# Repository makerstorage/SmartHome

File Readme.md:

This repo is for our iot products

And our store at

http://makerstorage.com/index.php

We enjoy sharing theses ideas with you all and any contributions, comments and or feedback is invited.

Community, Collaboration and Sharing is our most important assets.

This Project is Open Source and is licensed under the Creative Commons 3.0.

https://creativecommons.org/licenses/by-sa/3.0/

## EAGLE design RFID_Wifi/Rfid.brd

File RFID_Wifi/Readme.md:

RFID WIFI Board

For more details, check out the product pages at

http://makerstorage.com/index.php?id_product=26&controller=product

MakerStorage invests time and resources providing this open source design, please support MakerStorage and open-source hardware by purchasing products from MakerStorage!

Designed by MakerStorage LLC.

Creative Commons Attribution, Share-Alike license, check https://creativecommons.org/licenses/by-sa/3.0/ for more information All text above must be included in any redistribution

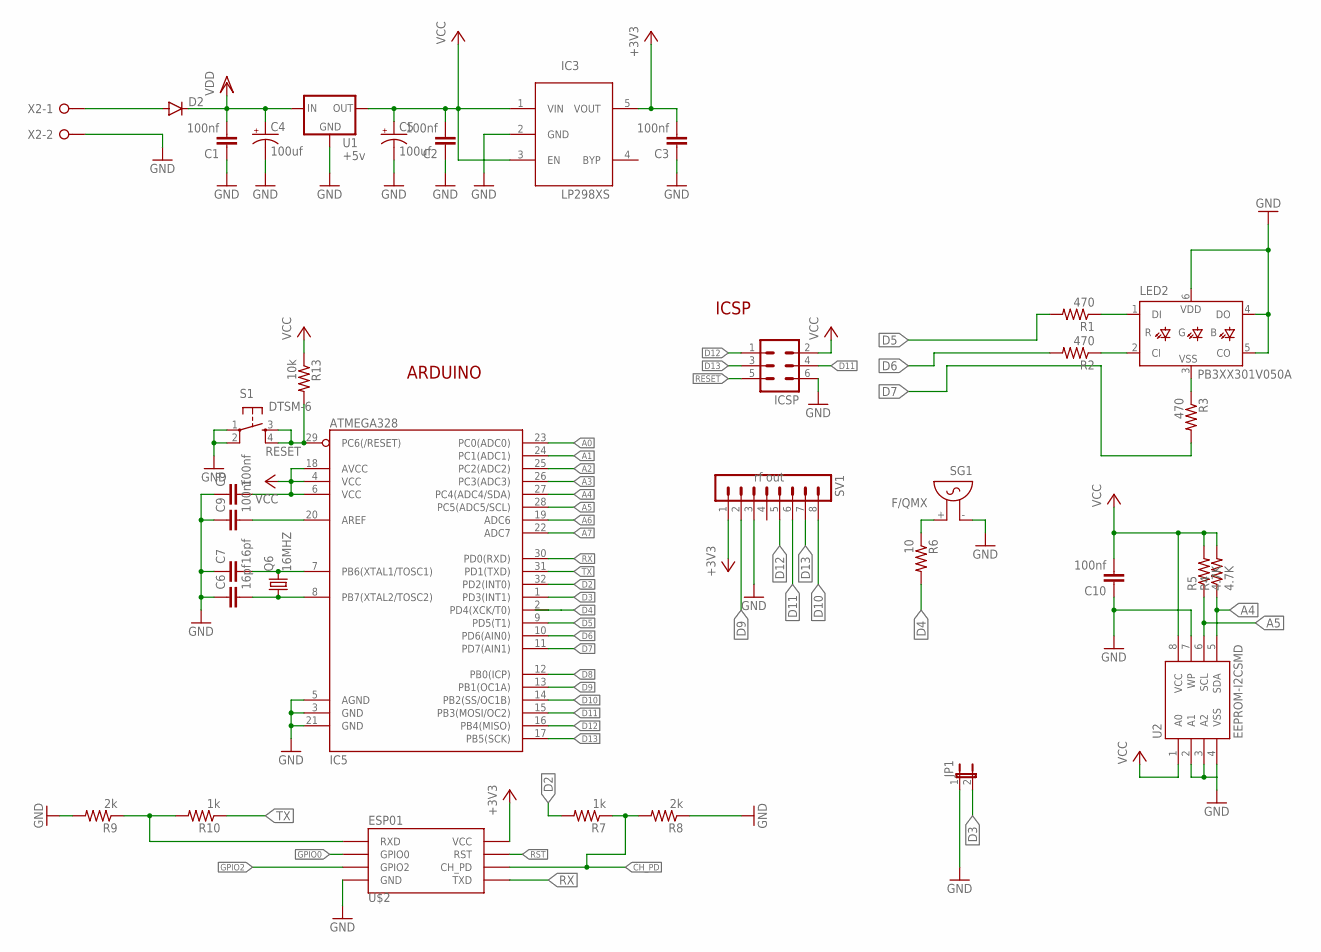
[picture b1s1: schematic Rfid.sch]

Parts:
C1, C2, C3, C8, C9, C10: 100nf; C0805
C4, C5: 100uf; PANASONIC_D
C6, C7: 16pf; C0805
D2: DIODESMA-ALT; SMA-DIODE_ALT
IC3: LP298XS; SOT23-5L
IC5: ATMEGA328; TQFP32-08
ICSP: ML6
JP1: JUMPER-2PTH; 1X02
LED2: PB3XX301V050A
Q6: 16MHZ; HC49/S
R1, R2, R3: 470; R0805
R4, R5: 4.7K; R0805
R6: 10; R0805
R7, R10: 1k; R0805
R8, R9: 2k; R0805
R13: 10k; R0805
S1: DTSM-6
SG1: F/QMX
SV1: MA08-1
U1: +5v; TO-252
U2: EEPROM-I2CSMD; SO08
U$2: ESP01
X2: W237-02P; W237-132

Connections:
+3V3: C3.2, IC3.5 (VOUT), SV1.1, U$2.VCC
A0: IC5.23 (PC0(ADC0))
A1: IC5.24 (PC1(ADC1))
A2: IC5.25 (PC2(ADC2))
A3: IC5.26 (PC3(ADC3))
A4: IC5.27 (PC4(ADC4/SDA)), R4.1, U2.5 (SDA)
A5: IC5.28 (PC5(ADC5/SCL)), R5.1, U2.6 (SCL)
A6: IC5.19 (ADC6)
A7: IC5.22 (ADC7)
CH_PD: R7.1, R8.2, U$2.CH_PD
D2: IC5.32 (PD2(INT0)), R7.2
D3: IC5.1 (PD3(INT1)), JP1.2
D4: IC5.2 (PD4(XCK/T0)), R6.2
D5: IC5.9 (PD5(T1)), R1.2
D6: IC5.10 (PD6(AIN0)), R2.2
D7: IC5.11 (PD7(AIN1)), R3.2
D8: IC5.12 (PB0(ICP))
D9: IC5.13 (PB1(OC1A)), SV1.2
D10: IC5.14 (PB2(SS/OC1B)), SV1.8
D11: IC5.15 (PB3(MOSI/OC2)), ICSP.4, SV1.6
D12: IC5.16 (PB4(MISO)), ICSP.1, SV1.5
D13: IC5.17 (PB5(SCK)), ICSP.3, SV1.7
GND: C1.1, C2.1, C3.1, C4.-, C5.-, C6.1, C7.1, C8.1, C9.1, C10.1, IC3.2 (GND), IC5.3 (GND), IC5.5 (AGND), IC5.21 (GND), ICSP.6, JP1.1, LED2.4 (DO), LED2.5 (CO), LED2.6 (VDD), R8.1, R9.2, S1.1, S1.2, SG1.- (1), SV1.3, U1.3 (GND), U2.2 (A1), U2.3 (A2), U2.4 (VSS), U2.7 (WP), U$2.GND, X2.2
GPIO0: U$2.GPIO0
GPIO2: U$2.GPIO2
unnamed: R9.1, R10.2, U$2.RX (RXD)
unnamed: D2.A, X2.1
unnamed: LED2.1 (DI), R1.1
unnamed: LED2.2 (CI), R2.1
unnamed: LED2.3 (VSS), R3.1
unnamed: R6.1, SG1.+ (2)
unnamed: C7.2, IC5.7 (PB6(XTAL1/TOSC1)), Q6.2
unnamed: C6.2, IC5.8 (PB7(XTAL2/TOSC2)), Q6.1
unnamed: C9.2, IC5.20 (AREF)
RESET: IC5.29 (PC6(/RESET)), ICSP.5, R13.2, S1.3, S1.4
RST: U$2.RST
RX: IC5.30 (PD0(RXD)), U$2.TX (TXD)
TX: IC5.31 (PD1(TXD)), R10.1
VCC: C2.2, C5.+, C8.2, C10.2, IC3.1 (VIN), IC3.3 (EN), IC5.4 (VCC), IC5.6 (VCC), IC5.18 (AVCC), ICSP.2, R4.2, R5.2, R13.1, U1.2 (OUT), U2.1 (A0), U2.8 (VCC)
VDD: C1.2, C4.+, D2.C, U1.1 (IN)

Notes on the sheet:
ICSP
ARDUINO
rf out

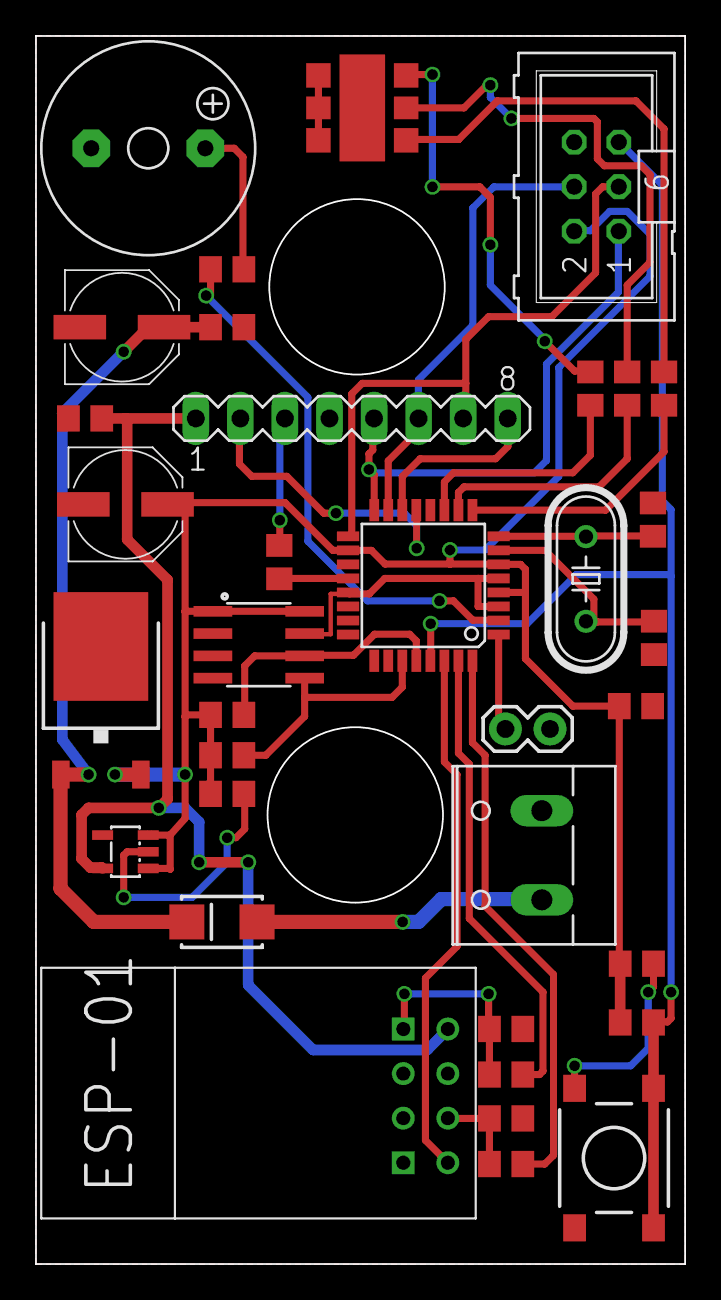
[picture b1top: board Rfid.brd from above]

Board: 2 copper layers, 37.0 x 70.0 mm, 35 parts (0 on the bottom side), 30 nets.

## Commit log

2017-01-14 relay board added
2017-01-14 RFID_WIFI Added

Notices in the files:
parts and their libraries:
SparkFun-DiscreteSemi: Licensing: Creative Commons ShareAlike 4.0 International - https://creativecommons.org/licenses/by-sa/4.0
